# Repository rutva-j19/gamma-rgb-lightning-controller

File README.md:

Gamma-Corrected RGB Lighting Controller

Project Overview:
This project implements a gamma-corrected RGB LED lighting controller that generates a smooth purple breathing light effect using PWM. The system combines a custom-designed PCB with a modular Verilog-based PWM engine and verified simulation waveforms.
The design focuses on practical digital logic, timing control, and manufacturable hardware.

What It Does:
- Generates PWM signals for RGB LEDs
- Applies gamma correction for perceptually smooth brightness
- Produces a breathing (fade in / fade out) animation
- Drives LEDs using low-side NMOS switching

Key Features:
- 3-channel PWM output
- Gamma LUT (4-bit brightness → 8-bit duty cycle)
- Parameterized tick generator
- Modular Verilog architecture
- Custom KiCad schematic and PCB layout
- Simulation-verified functionality(Performed using Icarus Verilog and GTK Wave)

Hardware Design:
- Low-side NMOS transistor switching for each LED channel
- Current-limiting resistors
- Header for PWM input signals
- Two-layer PCB designed in KiCad

Digital Design(Verilog modules):
- top.v – System integration and breathing control
- tick_gen.v – Timing pulse generator
- gamma_lut.v – Gamma correction lookup table
- pwm.v – PWM generator
- tb_top.v – Testbench

Future Improvements:
- Add a push-button interface to change colors and animation speed at runtime 
- Store multiple lighting profiles (solid, breathing, pulse) selectable at runtime
- Add UART or USB interface to control the LED behavior from a PC

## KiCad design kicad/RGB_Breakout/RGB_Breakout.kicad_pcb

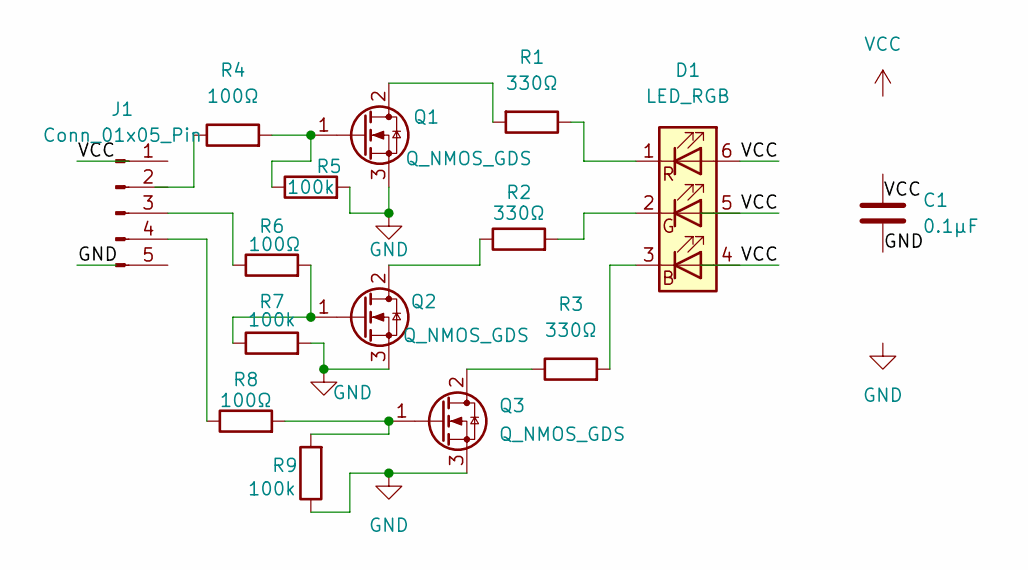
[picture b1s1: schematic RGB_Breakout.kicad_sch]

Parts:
C1: 0.1μF; C_0805_2012Metric
D1: LED_RGB; LED_RGB_5050-6
J1: Conn_01x05_Pin; PinHeader_1x05_P2.54mm_Vertical
Q1, Q2, Q3: Q_NMOS_GDS; SOT-23
R1, R2, R3: 330Ω; R_0805_2012Metric
R4, R6, R8: 100Ω; R_0805_2012Metric
R5, R7, R9: 100k; R_0805_2012Metric

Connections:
GND: C1.2, Q1.3 (S), Q2.3 (S), Q3.3 (S), R5.2, R7.2, R9.1
unnamed: D1.3 (BK), R3.2
unnamed: D1.2 (GK), R2.2
unnamed: D1.1 (RK), R1.1
unnamed: J1.3, R6.1
unnamed: J1.4, R8.1
unnamed: Q1.2 (D), R1.2
unnamed: Q1.1 (G), R4.2, R5.1
unnamed: Q2.2 (D), R2.1
unnamed: Q2.1 (G), R6.2, R7.1
unnamed: Q3.2 (D), R3.1
unnamed: Q3.1 (G), R8.2, R9.2
VCC: D1.4 (BA), D1.5 (GA), D1.6 (RA)

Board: 2 copper layers, 16 parts (0 on the bottom side), 13 nets, no tracks yet.

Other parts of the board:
H1: MountingHole_2.1mm

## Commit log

2026-02-03 Initial commit: KiCad RGB breakout + Verilog PWM breathing demo
2026-02-03 Add Schematic and README
2026-02-03 Revise Readme
